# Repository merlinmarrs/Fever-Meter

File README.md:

# Fever-Meter

Developed by Fablab Digiscope

Device to monitor temperature through body contact (perhaps at the forehead if attached to a visor) 
and alert if a fever temperature pattern is recognized.

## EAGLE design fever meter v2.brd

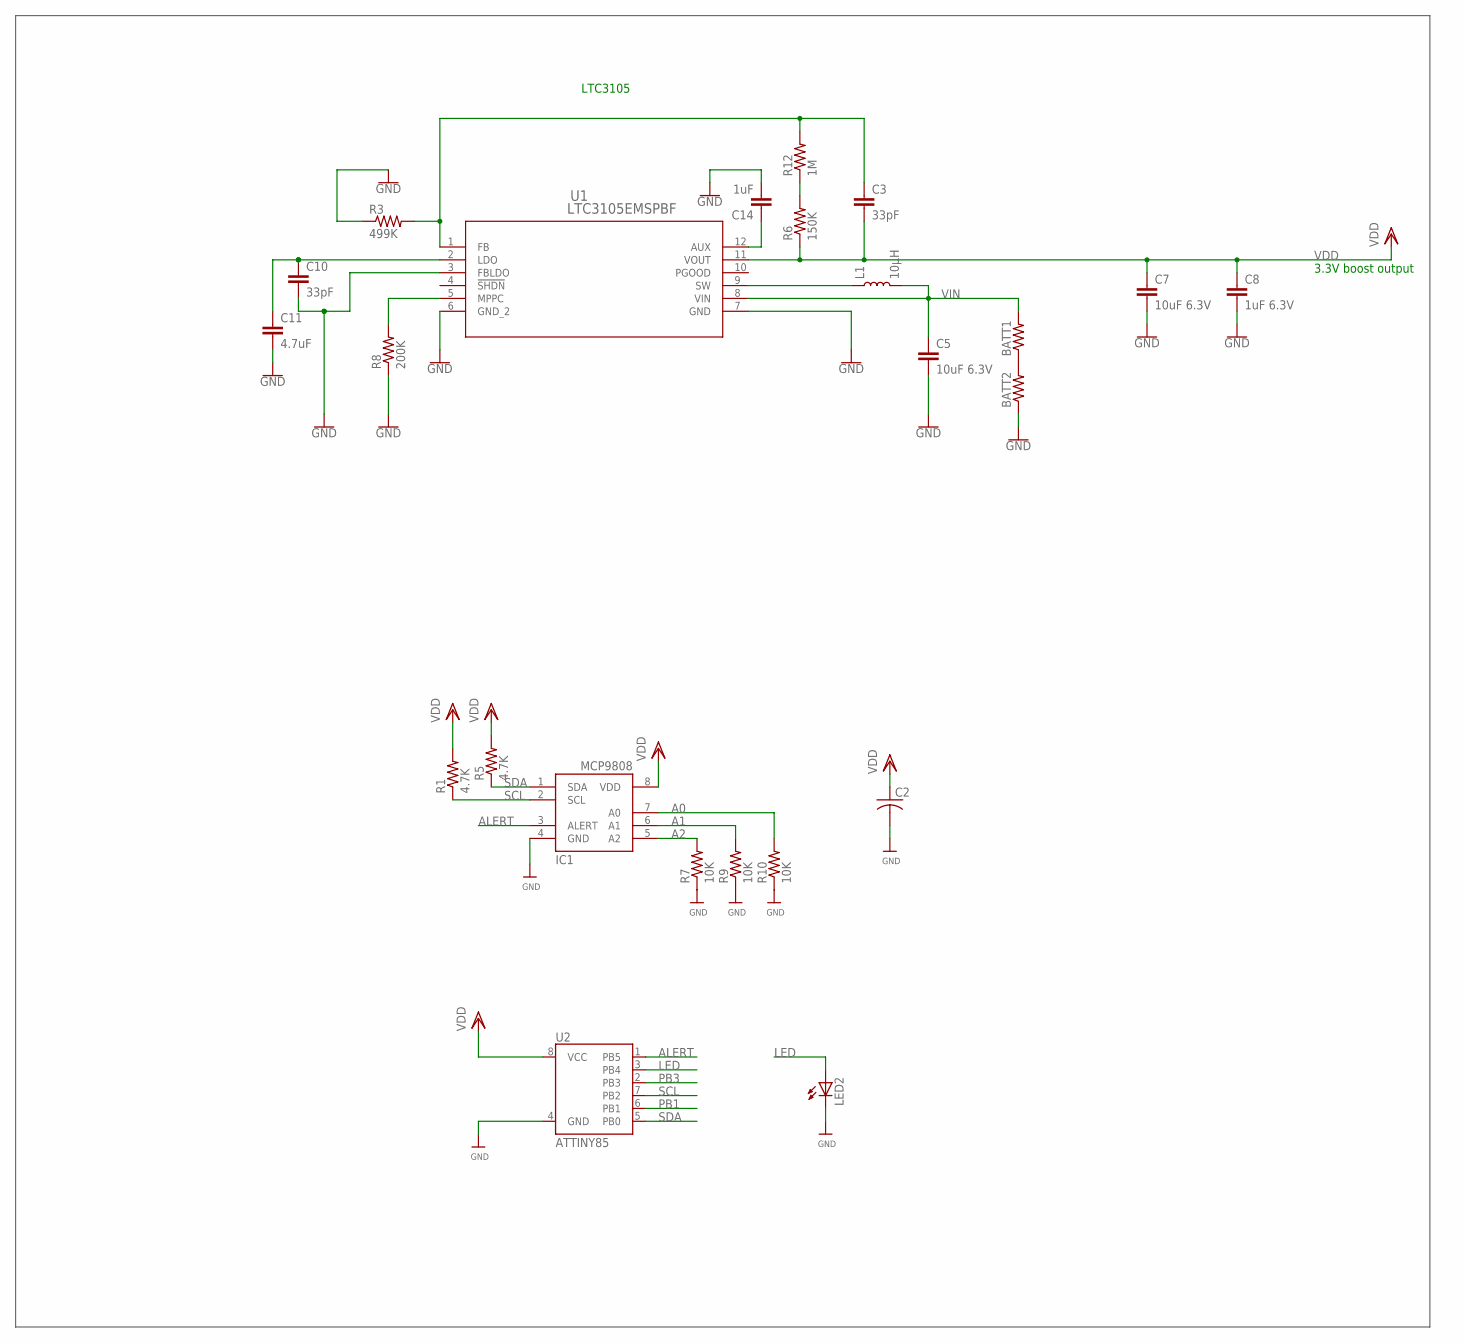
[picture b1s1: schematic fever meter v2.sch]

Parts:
BATT1, BATT2: R-US_M0805; M0805
C2: C-USC1206; C1206
C3, C10: 33pF; 1206
C5, C7: 10uF 6.3V; 1206
C8: 1uF 6.3V; 1206
C11: 4.7uF; 1206
C14: 1uF; 1206
IC1: MCP9808-E/MS; MSOP8_0.65MM
L1: 10µH; INDUCTOR_2.2UH
LED2: LEDSMT1206; 1206
R1, R5: 4.7K; M1206
R3: 499K; R1206
R6: 150K; R1206
R7, R9, R10: 10K; M1206
R8: 200K; R1206
R12: 1M; R1206
U1: LTC3105EMSPBF; MSOP-12_MS
U2: ATTINY85

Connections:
A0: IC1.7 (A0), R10.2
A1: IC1.6 (A1), R9.2
A2: IC1.5 (A2), R7.2
ALERT: IC1.3 (ALERT), U2.1 (PB5)
AUX: C14.1, U1.12 (AUX)
FB: C3.1, R3.2, R12.2, U1.1 (FB)
GND: BATT2.1, C2.2, C5.2, C7.2, C8.2, C10.2, C11.2, C14.2, IC1.4 (GND), LED2.C, R3.1, R7.1, R8.1, R9.1, R10.1, U1.3 (FBLDO), U1.6 (GND_2), U1.7 (GND), U2.4 (GND)
LDO: C10.1, C11.1, U1.2 (LDO)
LED: LED2.A, U2.3 (PB4)
MPPC: R8.2, U1.5 (MPPC)
unnamed: BATT1.1, BATT2.2
unnamed: R6.2, R12.1
PB1: U2.6 (PB1)
PB3: U2.2 (PB3)
SCL: IC1.2 (SCL), R1.1, U2.7 (PB2)
SDA: IC1.1 (SDA), R5.1, U2.5 (PB0)
SW: L1.P$1 (1), U1.9 (SW)
VDD: C2.1, C3.2, C7.1, C8.1, IC1.8 (VDD), R1.2, R5.2, R6.1, U1.11 (VOUT), U2.8 (VCC)
VIN: BATT1.2, C5.1, L1.P$2 (2), U1.8 (VIN)

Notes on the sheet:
3.3V boost output
LTC3105

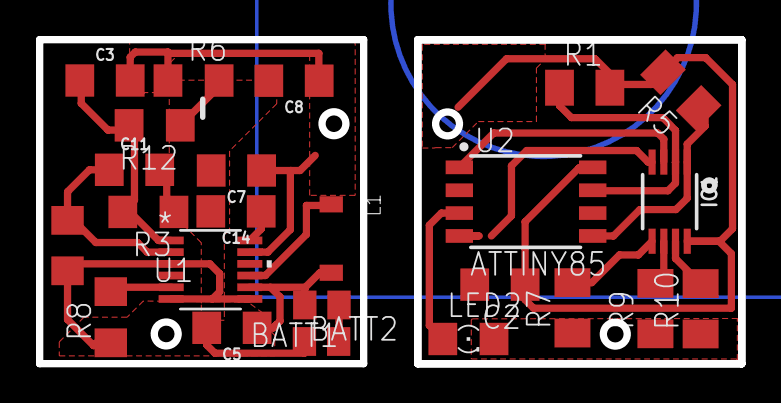
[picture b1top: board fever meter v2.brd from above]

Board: 2 copper layers, 39.0 x 18.0 mm, 24 parts (0 on the bottom side), 17 nets.

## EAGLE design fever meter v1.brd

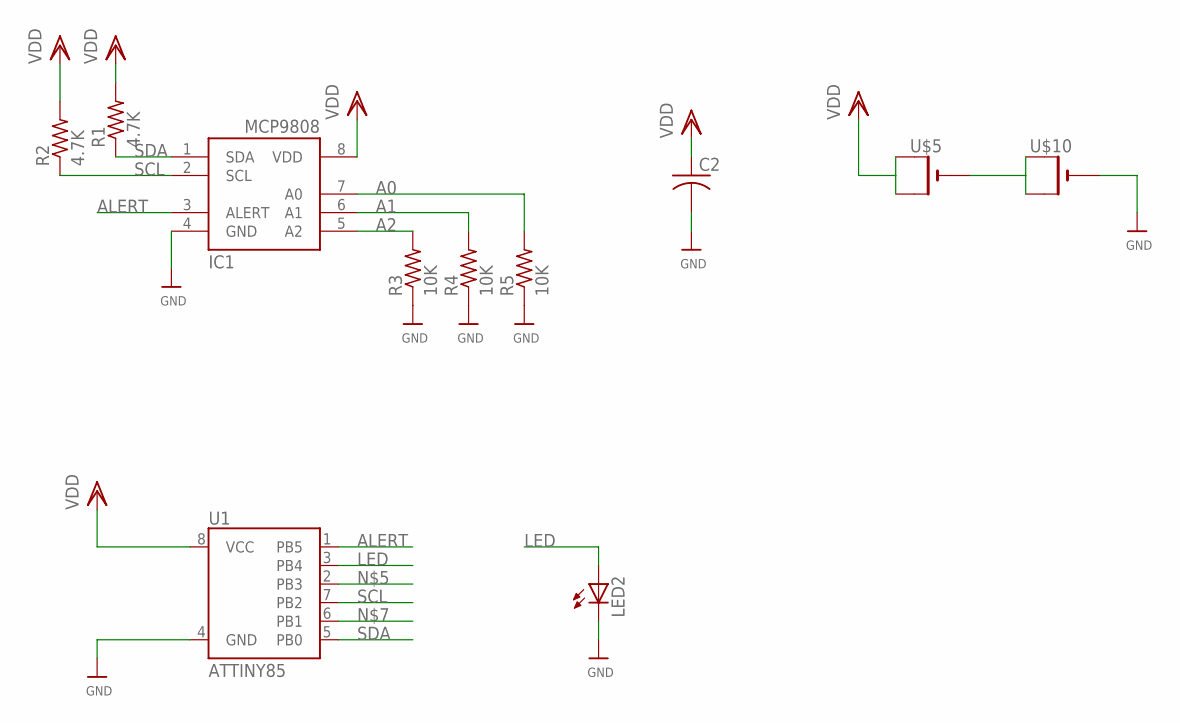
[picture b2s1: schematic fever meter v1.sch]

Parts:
C2: C-USC1206; C1206
IC1: MCP9808-E/MS; MSOP8_0.65MM
LED2: LEDSMT1206; 1206
R1, R2: 4.7K; M1206
R3, R4, R5: 10K; M1206
U1: ATTINY85
U$5, U$10: CR1220SMT; CR1220-SMD

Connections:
A0: IC1.7 (A0), R5.2
A1: IC1.6 (A1), R4.2
A2: IC1.5 (A2), R3.2
ALERT: IC1.3 (ALERT), U1.1 (PB5)
GND: C2.2, IC1.4 (GND), LED2.C, R3.1, R4.1, R5.1, U1.4 (GND), U$10.-
LED: LED2.A, U1.3 (PB4)
unnamed: U$5.-, U$10.+$1 (+), U$10.+$2 (+1)
SCL: IC1.2 (SCL), R2.1, U1.7 (PB2)
SDA: IC1.1 (SDA), R1.1, U1.5 (PB0)
VDD: C2.1, IC1.8 (VDD), R1.2, R2.2, U1.8 (VCC), U$5.+$1 (+), U$5.+$2 (+1)

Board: 2 copper layers, 11 parts (0 on the bottom side), 10 nets, no tracks yet.

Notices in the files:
parts and their libraries:
microbuilder: This work is placed in the public domain, and may be freely used for commercial and non-commercial work with the following conditions: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
SparkFun-IC-Microcontroller: Licensing: Creative Commons ShareAlike 4.0 International - https://creativecommons.org/licenses/by-sa/4.0
